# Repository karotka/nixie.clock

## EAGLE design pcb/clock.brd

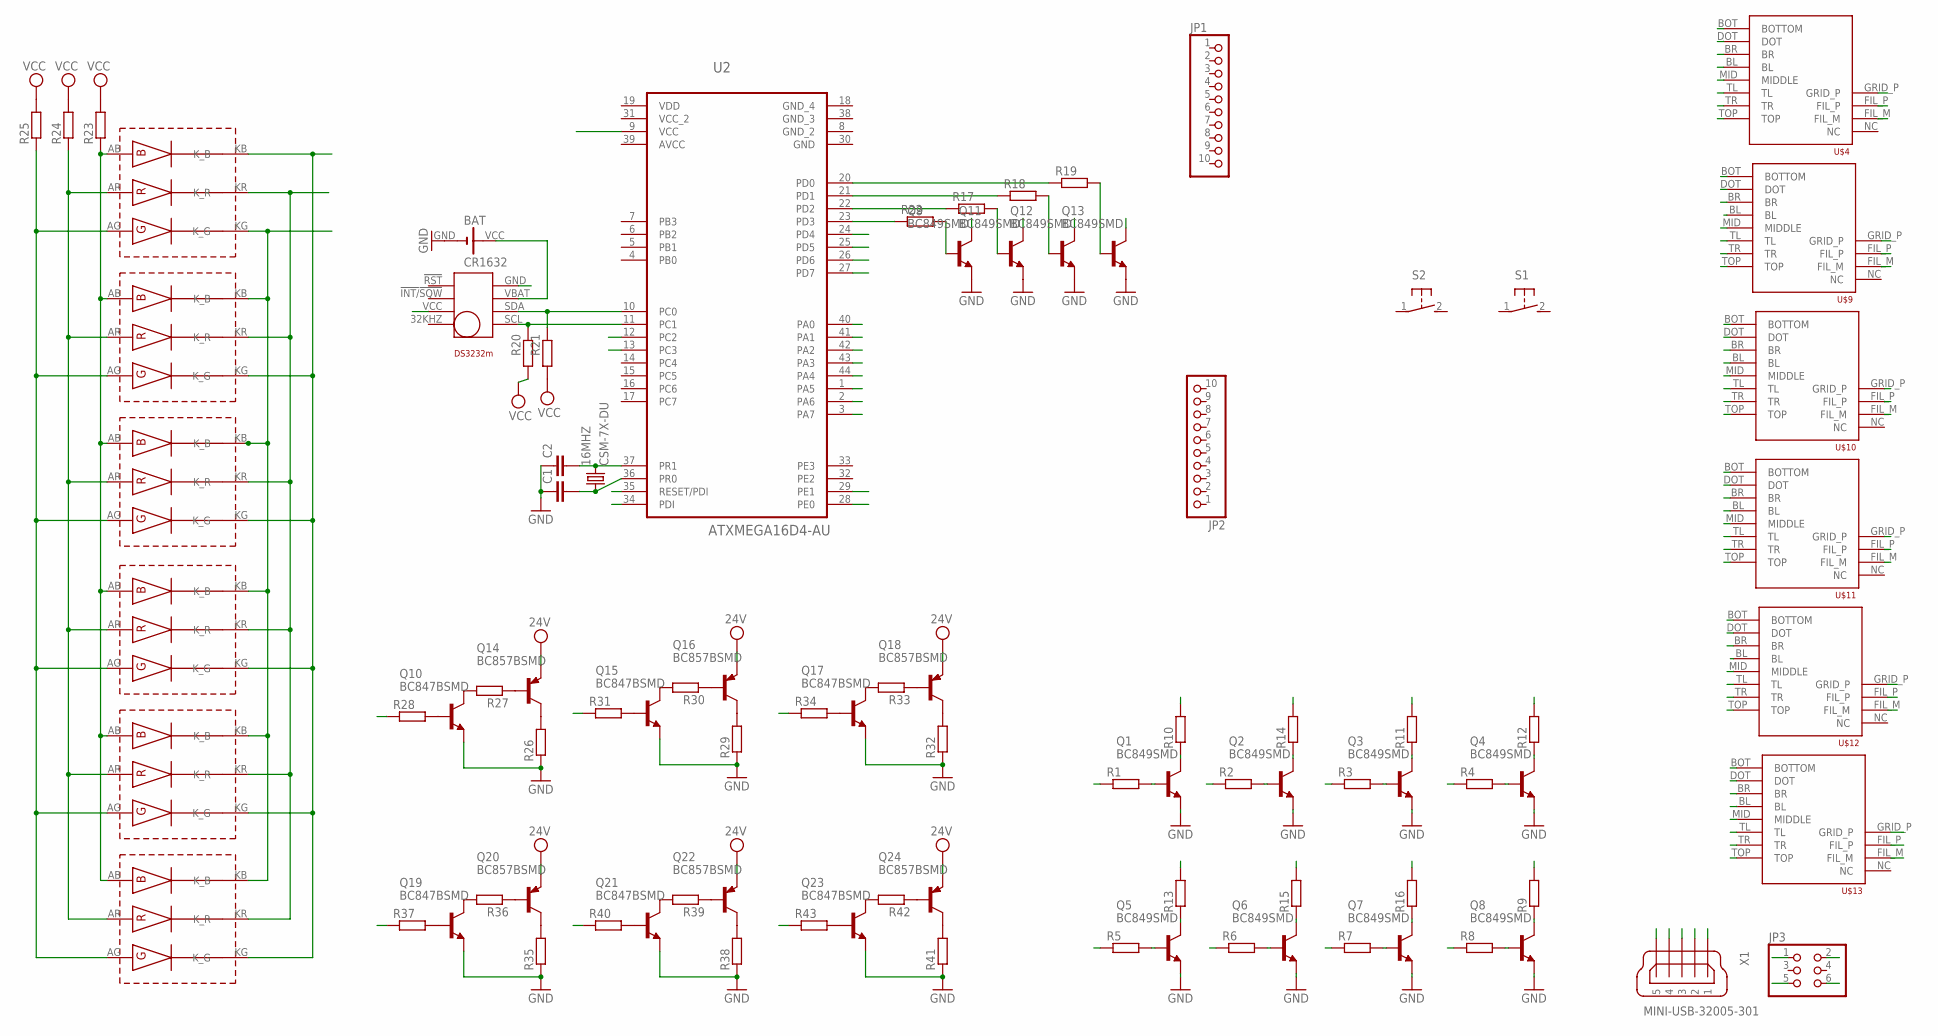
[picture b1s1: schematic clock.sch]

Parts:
16MHZ: CSM-7X-DU
BAT: CR1632; CR3232
C1, C2: C-EUC0805K; C0805K
JP1, JP2: PINHD-1X10; 1X10
JP3: PINHD-2X3/90; 2X03/90
Q1, Q2, Q3, Q4, Q5, Q6, Q7, Q8, Q9, Q11, Q12, Q13: BC849SMD; SOT23-BEC
Q10, Q15, Q17, Q19, Q21, Q23: BC847BSMD; SOT23
Q14, Q16, Q18, Q20, Q22, Q24: BC857BSMD; SOT23-BEC
R1, R2, R3, R4, R5, R6, R7, R8, R9, R10, R11, R12, R13, R14, R15, R16, R17, R18, R19, R20, R21, R22, R23, R24, R25, R26, R27, R28, R29, R30, R31, R32, R33, R34, R35, R36, R37, R38, R39, R40, R41, R42, R43: R-EU_0207/10; 0207/10
S1, S2: 31-XX; B3F-31XX
U2: ATXMEGA16D4-AU; QFP80P1200X1200X120-44N
U$1, U$3, U$5, U$6, U$7, U$8: RGB-SMT-SQUARE5X5MM; SMT-SQUARE5
U$2: DS3232M; SOIC8
U$4, U$9, U$10, U$11, U$12, U$13: IV6_NUMITRONLARGE; IV6_NUMITRON_PAC_LARGE
X1: MINI-USB-32005-301; 32005-301

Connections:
24V: Q14.E, Q16.E, Q18.E, Q20.E, Q22.E, Q24.E
AVCC: U2.39 (AVCC)
B: Q11.C, U$1.KB (K_B), U$3.KG (K_G), U$5.KG (K_G), U$6.KG (K_G), U$7.KG (K_G), U$8.KG (K_G)
BL: U$4.BL, U$9.BL, U$10.BL, U$11.BL, U$12.BL, U$13.BL
BOT: U$4.BOT (BOTTOM), U$9.BOT (BOTTOM), U$10.BOT (BOTTOM), U$11.BOT (BOTTOM), U$12.BOT (BOTTOM), U$13.BOT (BOTTOM)
BR: U$4.BR, U$9.BR, U$10.BR, U$11.BR, U$12.BR, U$13.BR
DOT: U$4.DOT, U$9.DOT, U$10.DOT, U$11.DOT, U$12.DOT, U$13.DOT
FILL_MINUS: Q9.C
FIL_P: U$4.FIL_P, U$9.FIL_P, U$10.FIL_P, U$11.FIL_P, U$12.FIL_P, U$13.FIL_P
G: Q12.C, U$1.KG (K_G), U$3.KB (K_B), U$5.KB (K_B), U$6.KB (K_B), U$7.KB (K_B), U$8.KB (K_B)
GND: BAT.GND (-), C1.1, C2.1, JP3.6, Q1.E, Q2.E, Q3.E, Q4.E, Q5.E, Q6.E, Q7.E, Q8.E, Q9.E, Q10.2 (E), Q11.E, Q12.E, Q13.E, Q15.2 (E), Q17.2 (E), Q19.2 (E), Q21.2 (E), Q23.2 (E), R26.1, R29.1, R32.1, R35.1, R38.1, R41.1, U$2.GND, X1.1, X1.2
MID: U$4.MID (MIDDLE), U$9.MID (MIDDLE), U$10.MID (MIDDLE), U$11.MID (MIDDLE), U$12.MID (MIDDLE), U$13.MID (MIDDLE)
unnamed: Q14.C, R26.2
unnamed: Q14.B, R27.1
unnamed: Q16.C, R29.2
unnamed: 16MHZ.1, C1.2, U2.36 (PR0)
unnamed: Q16.B, R30.1
unnamed: Q18.C, R32.2
unnamed: Q8.B, R8.2
unnamed: Q1.B, R1.2
unnamed: Q3.B, R3.2
unnamed: Q4.B, R4.2
unnamed: Q5.B, R5.2
unnamed: Q2.B, R2.2
unnamed: Q6.B, R6.2
unnamed: Q7.B, R7.2
unnamed: Q18.B, R33.1
unnamed: Q1.C, R10.1
unnamed: Q4.C, R12.1
unnamed: Q5.C, R13.1
unnamed: Q2.C, R14.1
unnamed: Q7.C, R16.1
unnamed: R20.1, U2.11 (PC1), U$2.SCL
unnamed: Q20.C, R35.2
unnamed: Q20.B, R36.1
unnamed: BAT.VCC (+), U$2.VBAT
unnamed: Q9.B, R22.2
unnamed: Q22.C, R38.2
unnamed: Q10.3 (C), R27.2
unnamed: R22.1, U2.23 (PD3)
unnamed: R23.1, U$1.AB (ANODE_B), U$3.AB (ANODE_B), U$5.AB (ANODE_B), U$6.AB (ANODE_B), U$7.AB (ANODE_B), U$8.AB (ANODE_B)
unnamed: R24.1, U$1.AR (ANODE_R), U$3.AR (ANODE_R), U$5.AR (ANODE_R), U$6.AR (ANODE_R), U$7.AR (ANODE_R), U$8.AR (ANODE_R)
unnamed: R25.1, U$1.AG (ANODE_G), U$3.AG (ANODE_G), U$5.AG (ANODE_G), U$6.AG (ANODE_G), U$7.AG (ANODE_G), U$8.AG (ANODE_G)
unnamed: R17.1, U2.22 (PD2)
unnamed: R18.1, U2.21 (PD1)
unnamed: R19.1, U2.20 (PD0)
unnamed: Q11.B, R17.2
unnamed: Q12.B, R18.2
unnamed: Q13.B, R19.2
unnamed: Q10.1 (B), R28.2
unnamed: Q15.3 (C), R30.2
unnamed: Q15.1 (B), R31.2
unnamed: Q22.B, R39.1
unnamed: Q17.3 (C), R33.2
unnamed: Q17.1 (B), R34.2
unnamed: Q24.C, R41.2
unnamed: Q19.3 (C), R36.2
unnamed: Q19.1 (B), R37.2
unnamed: Q24.B, R42.1
unnamed: Q21.3 (C), R39.2
unnamed: Q21.1 (B), R40.2
unnamed: Q23.3 (C), R42.2
unnamed: Q23.1 (B), R43.2
unnamed: Q3.C, R11.1
unnamed: Q6.C, R15.1
unnamed: Q8.C, R9.1
PA0: R1.1, U2.40 (PA0)
PA1: R2.1, U2.41 (PA1)
PA2: R3.1, U2.42 (PA2)
PA3: R4.1, U2.43 (PA3)
PA4: R5.1, U2.44 (PA4)
PA5: R6.1, U2.1 (PA5)
PA6: R7.1, U2.2 (PA6)
PA7: R8.1, U2.3 (PA7)
PD4: R28.1, U2.24 (PD4)
PD5: R31.1, U2.25 (PD5)
PD6: R34.1, U2.26 (PD6)
PD7: R37.1, U2.27 (PD7)
PDI: JP3.1, U2.34 (PDI)
PE0: R40.1, U2.28 (PE0)
PE1: R43.1, U2.29 (PE1)
PR1: 16MHZ.2, C2.2, U2.37 (PR1)
R: Q13.C, U$1.KR (K_R), U$3.KR (K_R), U$5.KR (K_R), U$6.KR (K_R), U$7.KR (K_R), U$8.KR (K_R)
RESET: JP3.5, U2.35 (RESET/PDI)
RX: U2.12 (PC2), X1.4
SDA: R21.1, U2.10 (PC0), U$2.SDA
TL: U$4.TL, U$9.TL, U$10.TL, U$11.TL, U$12.TL, U$13.TL
TOP: U$4.TOP, U$9.TOP, U$10.TOP, U$11.TOP, U$12.TOP, U$13.TOP
TR: U$4.TR, U$9.TR, U$10.TR, U$11.TR, U$12.TR, U$13.TR
TX: U2.13 (PC3), X1.3
UB: R16.2
VCC: JP3.2, R20.2, R21.2, R23.2, R24.2, R25.2, U2.9 (VCC), U$2.VCC, X1.5
VCC_2: U2.31 (VCC_2)
VDD: U2.19 (VDD)

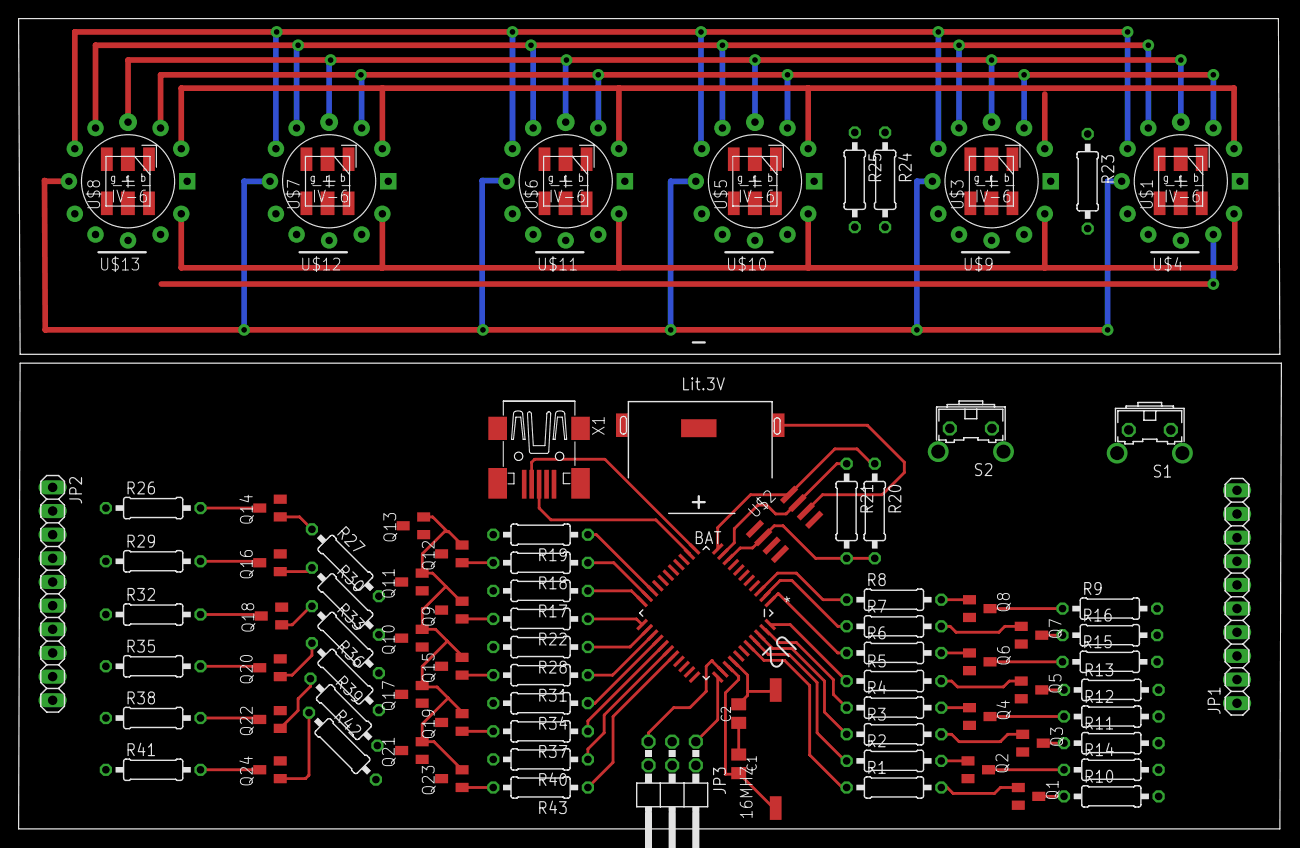
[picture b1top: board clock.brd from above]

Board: 2 copper layers, 135.6 x 87.0 mm, 91 parts (0 on the bottom side), 89 nets.

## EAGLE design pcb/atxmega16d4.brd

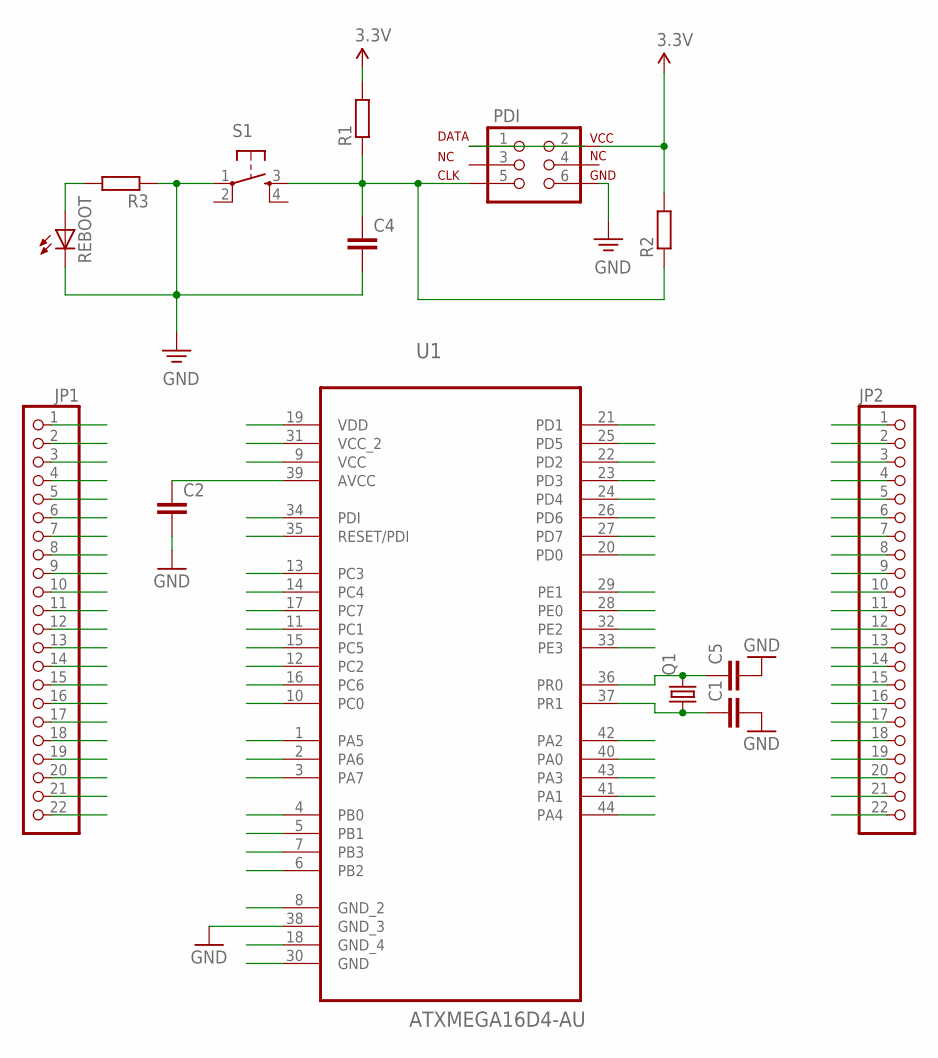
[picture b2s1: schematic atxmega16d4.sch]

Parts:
C1, C2, C5: C-EU025-025X050; C025-025X050
C4: C-EU025-040X050; C025-040X050
JP1, JP2: PINHD-1X22; 1X22
PDI: XMEGA_PDI_PRGNS; 2X3-NS
Q1: CRYSTALHC49U-V; HC49U-V
R1: R-EU_0309/10; 0309/10
R2, R3: R-EU_0207/10; 0207/10
REBOOT: LED3MM
S1: TAC_SWITCHPTH; TACTILE-PTH
U1: ATXMEGA16D4-AU; QFP80P1200X1200X120-44N

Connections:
3.3V: C2.1, JP1.9, JP1.19, JP2.9, JP2.17, PDI.2, R1.2, R2.2, U1.9 (VCC), U1.19 (VDD), U1.31 (VCC_2), U1.39 (AVCC)
GND: C1.2, C2.2, C4.2, C5.2, JP1.8, JP1.18, JP2.8, JP2.16, PDI.6, R3.1, REBOOT.K (C), S1.1, U1.8 (GND_2), U1.18 (GND_4), U1.30 (GND), U1.38 (GND_3)
unnamed: R3.2, REBOOT.A
PA0: JP2.18, U1.40 (PA0)
PA1: JP2.19, U1.41 (PA1)
PA2: JP2.20, U1.42 (PA2)
PA3: JP2.21, U1.43 (PA3)
PA4: JP2.22, U1.44 (PA4)
PA5: JP1.1, U1.1 (PA5)
PA6: JP1.2, U1.2 (PA6)
PA7: JP1.3, U1.3 (PA7)
PB0: JP1.4, U1.4 (PB0)
PB1: JP1.5, U1.5 (PB1)
PB2: JP1.6, U1.6 (PB2)
PB3: JP1.7, U1.7 (PB3)
PC0: JP1.10, U1.10 (PC0)
PC1: JP1.11, U1.11 (PC1)
PC2: JP1.12, U1.12 (PC2)
PC3: JP1.13, U1.13 (PC3)
PC4: JP1.14, U1.14 (PC4)
PC5: JP1.15, U1.15 (PC5)
PC6: JP1.16, U1.16 (PC6)
PC7: JP1.17, U1.17 (PC7)
PD0: JP1.20, U1.20 (PD0)
PD1: JP1.21, U1.21 (PD1)
PD2: JP1.22, U1.22 (PD2)
PD3: JP2.1, U1.23 (PD3)
PD4: JP2.2, U1.24 (PD4)
PD5: JP2.3, U1.25 (PD5)
PD6: JP2.4, U1.26 (PD6)
PD7: JP2.5, U1.27 (PD7)
PDI: JP2.12, PDI.1, U1.34 (PDI)
PE0: JP2.6, U1.28 (PE0)
PE1: JP2.7, U1.29 (PE1)
PE2: JP2.10, U1.32 (PE2)
PE3: JP2.11, U1.33 (PE3)
PR0: C5.1, JP2.14, Q1.2, U1.36 (PR0)
PR1: C1.1, JP2.15, Q1.1, U1.37 (PR1)
RESET: C4.1, JP2.13, PDI.5, R1.1, R2.1, S1.3, U1.35 (RESET/PDI)

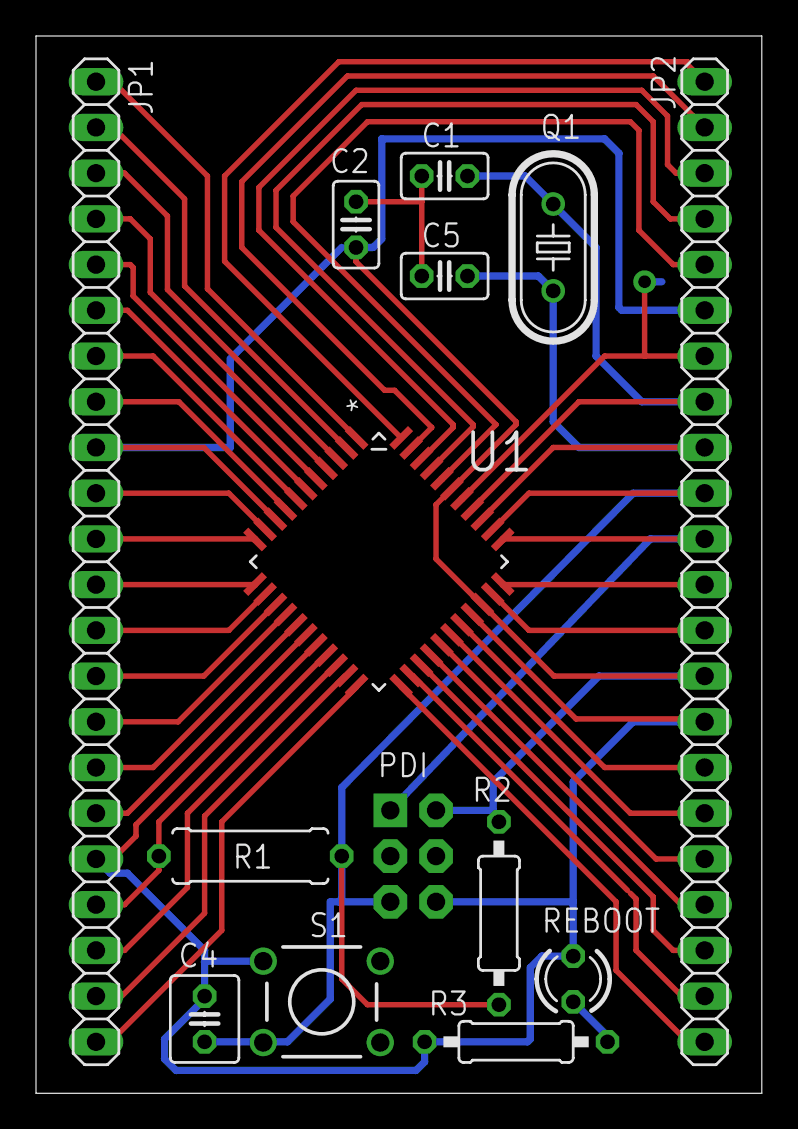
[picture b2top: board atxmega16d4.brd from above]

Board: 2 copper layers, 40.3 x 58.7 mm, 14 parts (0 on the bottom side), 39 nets.

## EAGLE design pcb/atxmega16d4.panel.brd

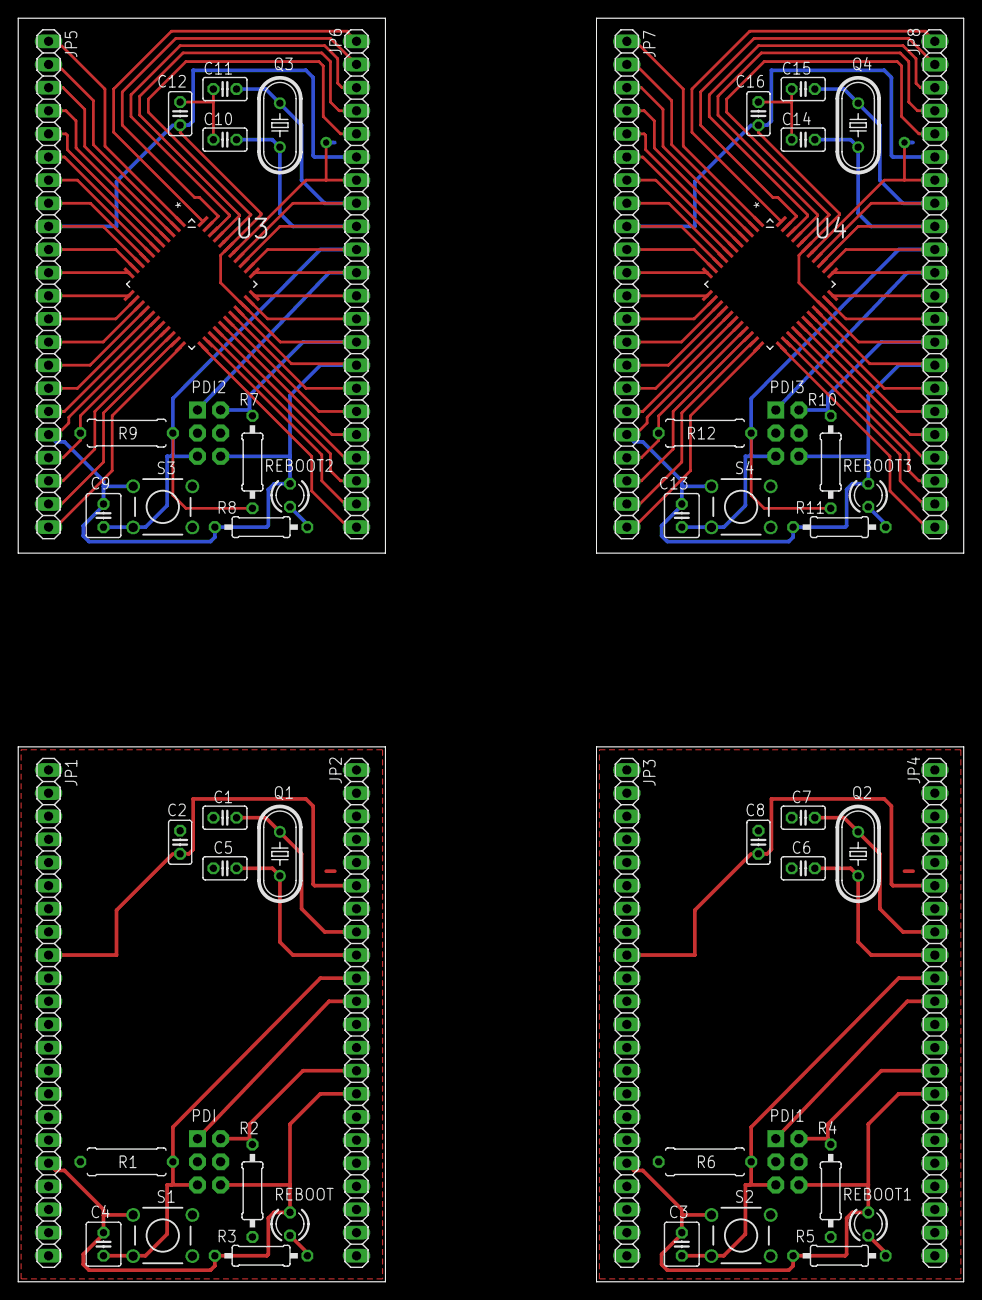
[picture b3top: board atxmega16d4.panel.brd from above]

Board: 2 copper layers, 103.8 x 138.7 mm, 54 parts (0 on the bottom side), 92 nets.

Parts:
C1, C2, C5, C6, C7, C8, C10, C11, C12, C14, C15, C16: C025-025X050
C3, C4, C9, C13: C025-040X050
JP1, JP2, JP3, JP4, JP5, JP6, JP7, JP8: 1X22
PDI, PDI1, PDI2, PDI3: 2X3-NS
Q1, Q2, Q3, Q4: HC49U-V
R1, R6, R9, R12: 0309/10
R2, R3, R4, R5, R7, R8, R10, R11: 0207/10
REBOOT, REBOOT1, REBOOT2, REBOOT3: LED3MM
S1, S2, S3, S4: TACTILE-PTH
U3, U4: ATXMEGA16D4-AU; QFP80P1200X1200X120-44N

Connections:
3.3V: C2.1, JP1.9, JP1.19, JP2.9, JP2.17, PDI.2, R1.2, R2.2
3.3V1: C8.1, JP3.9, JP3.19, JP4.9, JP4.17, PDI1.2, R4.2, R6.2
3.3V2: C12.1, JP5.9, JP5.19, JP6.9, JP6.17, PDI2.2, R7.2, R9.2, U3.9, U3.19, U3.31, U3.39
3.3V3: C16.1, JP7.9, JP7.19, JP8.9, JP8.17, PDI3.2, R10.2, R12.2, U4.9, U4.19, U4.31, U4.39
GND: C1.2, C2.2, C4.2, C5.2, JP1.8, JP1.18, JP2.8, JP2.16, PDI.6, R3.1, REBOOT.K, S1.1
GND1: C3.2, C6.2, C7.2, C8.2, JP3.8, JP3.18, JP4.8, JP4.16, PDI1.6, R5.1, REBOOT1.K, S2.1
GND2: C9.2, C10.2, C11.2, C12.2, JP5.8, JP5.18, JP6.8, JP6.16, PDI2.6, R8.1, REBOOT2.K, S3.1, U3.8, U3.18, U3.30, U3.38
GND3: C13.2, C14.2, C15.2, C16.2, JP7.8, JP7.18, JP8.8, JP8.16, PDI3.6, R11.1, REBOOT3.K, S4.1, U4.8, U4.18, U4.30, U4.38
unnamed: R5.2, REBOOT1.A
unnamed: R8.2, REBOOT2.A
unnamed: R11.2, REBOOT3.A
unnamed: R3.2, REBOOT.A
PA16: JP5.1, U3.1
PA17: JP5.2, U3.2
PA18: JP5.3, U3.3
PA19: JP6.20, U3.42
PA20: JP6.18, U3.40
PA21: JP6.21, U3.43
PA22: JP6.19, U3.41
PA23: JP6.22, U3.44
PA24: JP7.1, U4.1
PA25: JP7.2, U4.2
PA26: JP7.3, U4.3
PA27: JP8.20, U4.42
PA28: JP8.18, U4.40
PA29: JP8.21, U4.43
PA30: JP8.19, U4.41
PA31: JP8.22, U4.44
PB8: JP5.4, U3.4
PB9: JP5.5, U3.5
PB10: JP5.7, U3.7
PB11: JP5.6, U3.6
PB12: JP7.4, U4.4
PB13: JP7.5, U4.5
PB14: JP7.7, U4.7
PB15: JP7.6, U4.6
PC16: JP5.10, U3.10
PC17: JP5.11, U3.11
PC18: JP5.12, U3.12
PC19: JP5.13, U3.13
PC20: JP5.14, U3.14
PC21: JP5.15, U3.15
PC22: JP5.16, U3.16
PC23: JP5.17, U3.17
PC24: JP7.10, U4.10
PC25: JP7.11, U4.11
PC26: JP7.12, U4.12
PC27: JP7.13, U4.13
PC28: JP7.14, U4.14
PC29: JP7.15, U4.15
PC30: JP7.16, U4.16
PC31: JP7.17, U4.17
PD16: JP5.21, U3.21
PD17: JP6.3, U3.25
PD18: JP5.22, U3.22
PD19: JP6.1, U3.23
PD20: JP6.2, U3.24
PD21: JP6.4, U3.26
PD22: JP6.5, U3.27
PD23: JP5.20, U3.20
PD24: JP7.21, U4.21
PD25: JP8.3, U4.25
PD26: JP7.22, U4.22
PD27: JP8.1, U4.23
PD28: JP8.2, U4.24
PD29: JP8.4, U4.26
PD30: JP8.5, U4.27
PD31: JP7.20, U4.20
PDI: JP2.12, PDI.1
PDI1: JP4.12, PDI1.1
PDI2: JP6.12, PDI2.1, U3.34
PDI3: JP8.12, PDI3.1, U4.34
PE8: JP6.7, U3.29
PE9: JP6.6, U3.28
PE10: JP6.10, U3.32
PE11: JP6.11, U3.33
PE12: JP8.7, U4.29
PE13: JP8.6, U4.28
PE14: JP8.10, U4.32
PE15: JP8.11, U4.33
PR0: C5.1, JP2.14, Q1.2
PR1: C1.1, JP2.15, Q1.1
PR2: C6.1, JP4.14, Q2.2
PR3: C7.1, JP4.15, Q2.1
PR4: C10.1, JP6.14, Q3.2, U3.36
PR5: C11.1, JP6.15, Q3.1, U3.37
PR6: C14.1, JP8.14, Q4.2, U4.36
PR7: C15.1, JP8.15, Q4.1, U4.37
RESET: C4.1, JP2.13, PDI.5, R1.1, R2.1, S1.3
RESET1: C3.1, JP4.13, PDI1.5, R4.1, R6.1, S2.3
RESET2: C9.1, JP6.13, PDI2.5, R7.1, R9.1, S3.3, U3.35
RESET3: C13.1, JP8.13, PDI3.5, R10.1, R12.1, S4.3, U4.35

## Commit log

2015-12-29 funkcni prototyp
2015-12-30 prociteni
2015-12-30 time reference
